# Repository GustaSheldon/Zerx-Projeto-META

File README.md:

# 🤖 Zerx-Projeto-META

  Projeto de mão robótica controlada por movimentos reais da mão de uma pessoa, interpretados usando encoders e um ESP32, que envia valores para o Arduino, através de comunicação bluetooth, para que servos sejam controlados em tempo real
  
## ℹ️ Sobre o projeto:
  Este projeto tem como objetivo o uso em fábricas e ambientes de trabalho que podem trazer perigos aos trabalhadores, para que um operário possa realizar seu trabalho através da mão robótica, não colocando seu membro em risco.
  Utilizando uma série de cordas presas a encoders, um ESP32 faz a leitura dos movimentos do usuário.
  Esses dados são então enviados, através de uma comunicação serial, para o Arduino, que os recebe e interpreta, para que possa controlar os servos de forma que repliquem os movimentos realizados pelo usuário
  
  Obs.: para programação do código do Arduino, foi usada a extensão PlatformIO do VsCode, não a ArduinoIDE
  
### ⚙️ Funcionalidades:
  - 📷 Rastreamento de movimentos da mão em tempo real com os encoders;
  - 📞 Comunicação bluetooth entre ESP32 e Arduino;
  - 🎮 Controle de servomotres para replicação dos movimentos captados;
  - 🔓 Sistema extensível para adicionar mais articulações e melhorias futuras

## 🔥 Projeto:

### Requisitos:
  - Python 3.x;
  - ESP32(ou similar)
  - 5 encoders
  - Arduino IDE(ou alternativa);
  - Arduino UNO(ou similiar);
  - Servomotores(5x para dedos, um por dedo)

### 🧩 Implementação:
  1. Clone este repositório:
      ```bash
     git clone https://github.com/GustaSheldon/Zerx-Projeto-META.git
     cd Zerx-Projeto-META
  2. Instale bibliotecas do Python:
     ```bash
     pip install opencv-python pyserial
  3. Abra e upe o código Arduino para seu microcontrolador
  4. Execute o script Python

### 🚀 Como usar:
  - Conecte os dois módulos(ESP32 com encoder + Arduino com servos) a qualquer fonte de energia.
  - Estabeleça a conxão bluetooth.
  - Veja os movimentos de um módulo serem replicados no outro em tempo real!

### 📓 Diário de bordo:
  ```bash
  https://docs.google.com/document/d/1PFmZ-JfQwFuOwu88TLG1hwXJkmD0gUxjG_UbMS_SyS4/edit?usp=sharing

testezinho

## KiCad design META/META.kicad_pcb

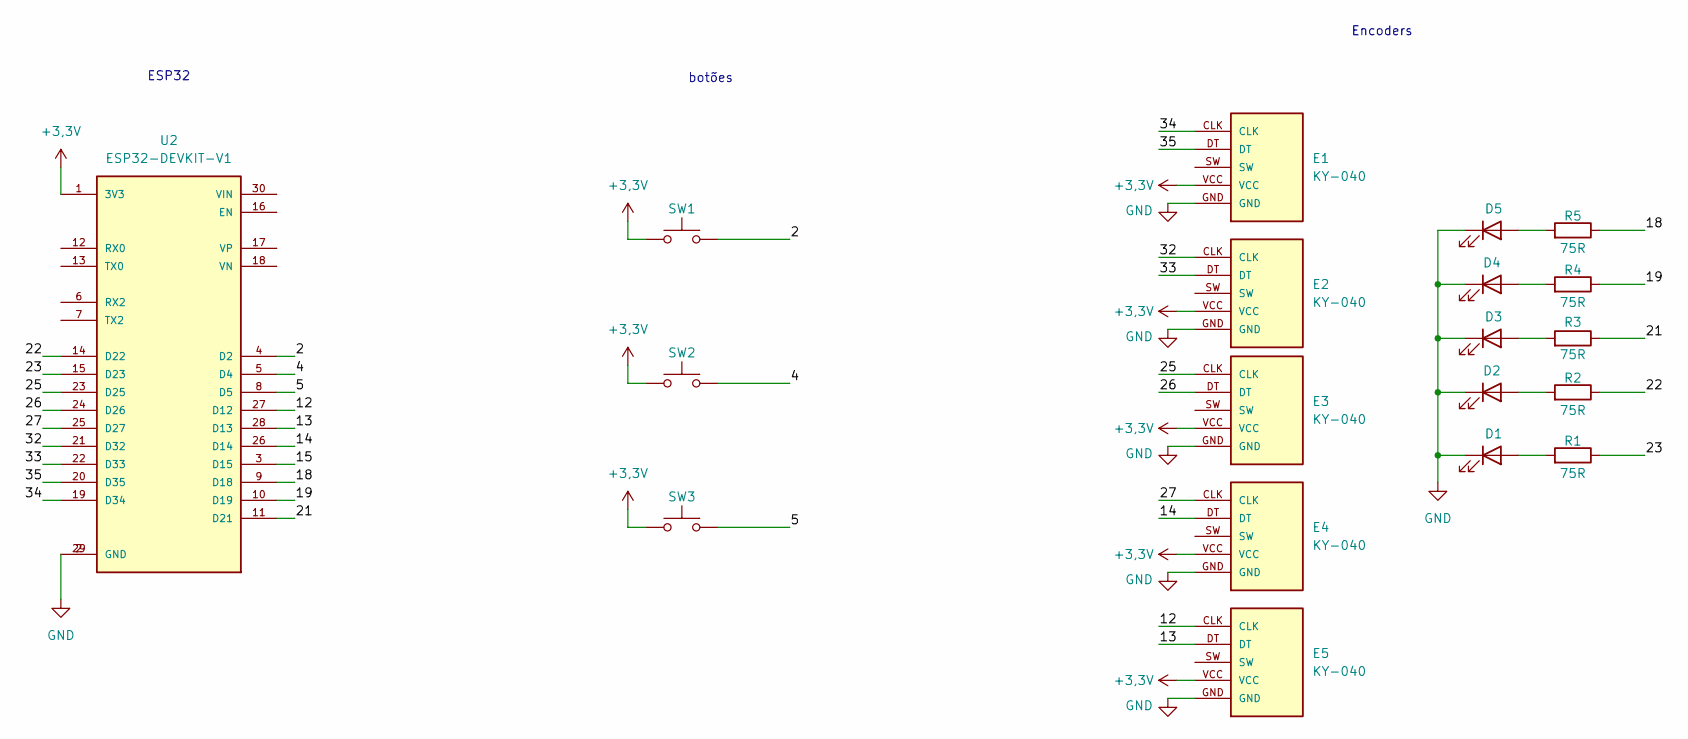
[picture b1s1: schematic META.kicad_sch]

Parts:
D1, D2, D3, D4, D5: LED; LED_D5.0mm_Clear
E1, E2, E3, E4, E5: KY-040; KY-040-PORT
R1, R2, R3, R4, R5: 75R; R_Axial_DIN0207_L6.3mm_D2.5mm_P10.16mm_Horizontal
SW1, SW2, SW3: SW_Push; SW_PUSH_6mm_H5mm
U2: ESP32-DEVKIT-V1; MODULE_ESP32_DEVKIT_V1; PARTREV N/A

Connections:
+3,3V: E1.VCC, E2.VCC, E3.VCC, E4.VCC, E5.VCC, SW1.1, SW2.1, SW3.1, U2.1 (3V3)
/2: SW1.2, U2.4 (D2)
/4: SW2.2, U2.5 (D4)
/5: SW3.2, U2.8 (D5)
/12: E5.CLK, U2.27 (D12)
/13: E5.DT, U2.28 (D13)
/14: E4.DT, U2.26 (D14)
/15: U2.3 (D15)
/18: R5.1, U2.9 (D18)
/19: R4.1, U2.10 (D19)
/21: R3.1, U2.11 (D21)
/22: R2.1, U2.14 (D22)
/23: R1.1, U2.15 (D23)
/25: E3.CLK, U2.23 (D25)
/26: E3.DT, U2.24 (D26)
/27: E4.CLK, U2.25 (D27)
/32: E2.CLK, U2.21 (D32)
/33: E2.DT, U2.22 (D33)
/34: E1.CLK, U2.19 (D34)
/35: E1.DT, U2.20 (D35)
GND: D1.1 (K), D2.1 (K), D3.1 (K), D4.1 (K), D5.1 (K), E1.GND, E2.GND, E3.GND, E4.GND, E5.GND, U2.2 (GND), U2.29 (GND)
unnamed: D1.2 (A), R1.2
unnamed: D2.2 (A), R2.2
unnamed: D3.2 (A), R3.2
unnamed: D4.2 (A), R4.2
unnamed: D5.2 (A), R5.2

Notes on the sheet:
Encoders
ESP32
botões

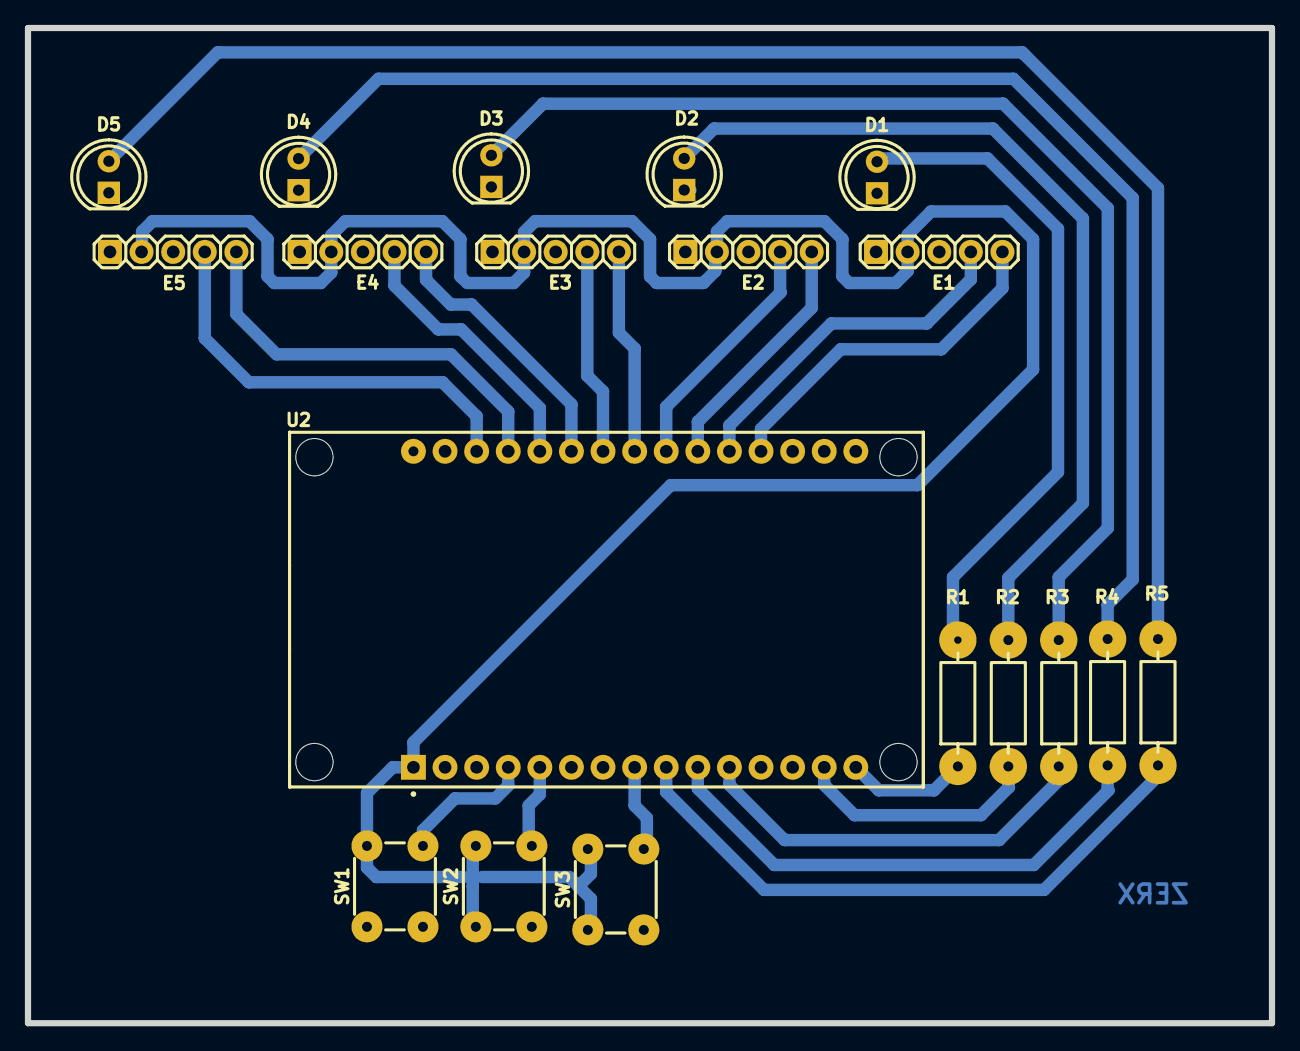
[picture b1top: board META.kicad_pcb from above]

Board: 2 copper layers, 100.0 x 80.0 mm, 19 parts (0 on the bottom side), 24 nets.

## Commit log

2025-04-05 README.md criado
    Criação do arquivo readme
2025-04-06 Adicionando o arquivo de código Arduino
    Código base, foi usado somente para teste da comunicação serial entre python e Arduino.
2025-04-06 Upando arquivos iniciais do programa em python
    Esses códigos são os iniciais do projeto, com as funcionalidades mais básicas, para que pudessem ser feitos testes iniciais.
2025-04-06 Upando código do Arduino
    Código usado para teste da comunicação serial python com Arduino.
2025-04-07 Update ZERX1.py
    code revamp
2025-06-08 Update README.md
    Mudança de direção e metodologias no projeto
2025-08-04 Delete SerialCom.py
    Excluído arquivo desnecessário à branch
2025-08-04 Delete ZERX1.py
    Excluído arquivo desnecessário à branch
2025-08-04 Delete main.cpp
    Excluído arquivo desnecessário à branch
2025-08-04 Atualizar o README.md
    Atualização do readme da branch de modelos 3D
2025-08-04 Adicionado modelo da caixa
    Adicionados os arquivos relacionados ao modelo da caixa do usuário
2025-08-04 Delete Modelo do usuário directory
    Diretório excluído por ter sido adicionado na branch errada
2025-08-04 Adicionado modelo da caixa
    Adicionados os arquivos referentes ao modelo da caixa, que será usada pelo usuário
2025-08-04 Adicionados modelos de paredes e tampa
    Adicionados os arquivos dos modelos das paredes e tampas, que são impressas separadamente da caixa do usuário
2025-08-04 Adicionado modelos de peças auxiliares
    Adicionados os arquivos referentes aos modelos das peças auxiliares à caixa, sendo o carretel e o anel que o usuário usará no dedo
2025-08-04 Adicionado modelo de teste para porca
    Arquivos do modelo para teste do buraco que deve conter uma porca, usado para prender as tampas, as paredes e os encoders na caixa
2025-08-04 Adicionados modelos para mão controlada
    Adicionados os arquivos dos modelos para impressão da mão que será controlada no projeto
2025-08-04 Update README.md
    Adicionado crédito para o modelo da mão robótica
2025-08-23 Atualização modelo do carretel
    Nesse novo modelo foi adicionada uma divisão para ter dois elástico no carretel, um para o usuário puxar, e o outro para fazer uma força contrária ao movimento do usuário, para retornar o carretel à 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
2025-08-24 Melhoras no código do openCV
    Comentários, novo sistema de referência, otimização do código.
2025-09-07 Delete main.cpp
    código caiu em desuso
2025-09-07 código encoder V1
    Controle para 1(um) encoder e servo
2025-09-12 Versão 3 do carretel
    Eixo vazado de fora a fora, e aumento da parede interna(que segura o elástico)
2025-09-12 Versão 2 da peça de teste da porca
    Aumento da espessura da parede lateral
2025-10-12 Versões dos códigos primitivos
    Versões dos códigos de testes isolados das funcionalidades do Arduino, para que possa ser integrado ao código final.
2025-10-12 Update ZERX1.py
    Adição de feedback visual com cores e limites para valores
2025-10-12 Add files via upload
    Added color feedback and variable limits
2025-10-13 Add files via upload
    Adição de movimento para servomotores
2025-10-18 Placa do projeto
    Placa e esquemático
2026-06-22 Arquivo teste
2026-06-22 Teste 2
2026-06-22 Teste Branche 1
